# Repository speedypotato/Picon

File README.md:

# Picon
A breakout board for the Raspberry Pi Pico for Yuancon or DIY Controllers

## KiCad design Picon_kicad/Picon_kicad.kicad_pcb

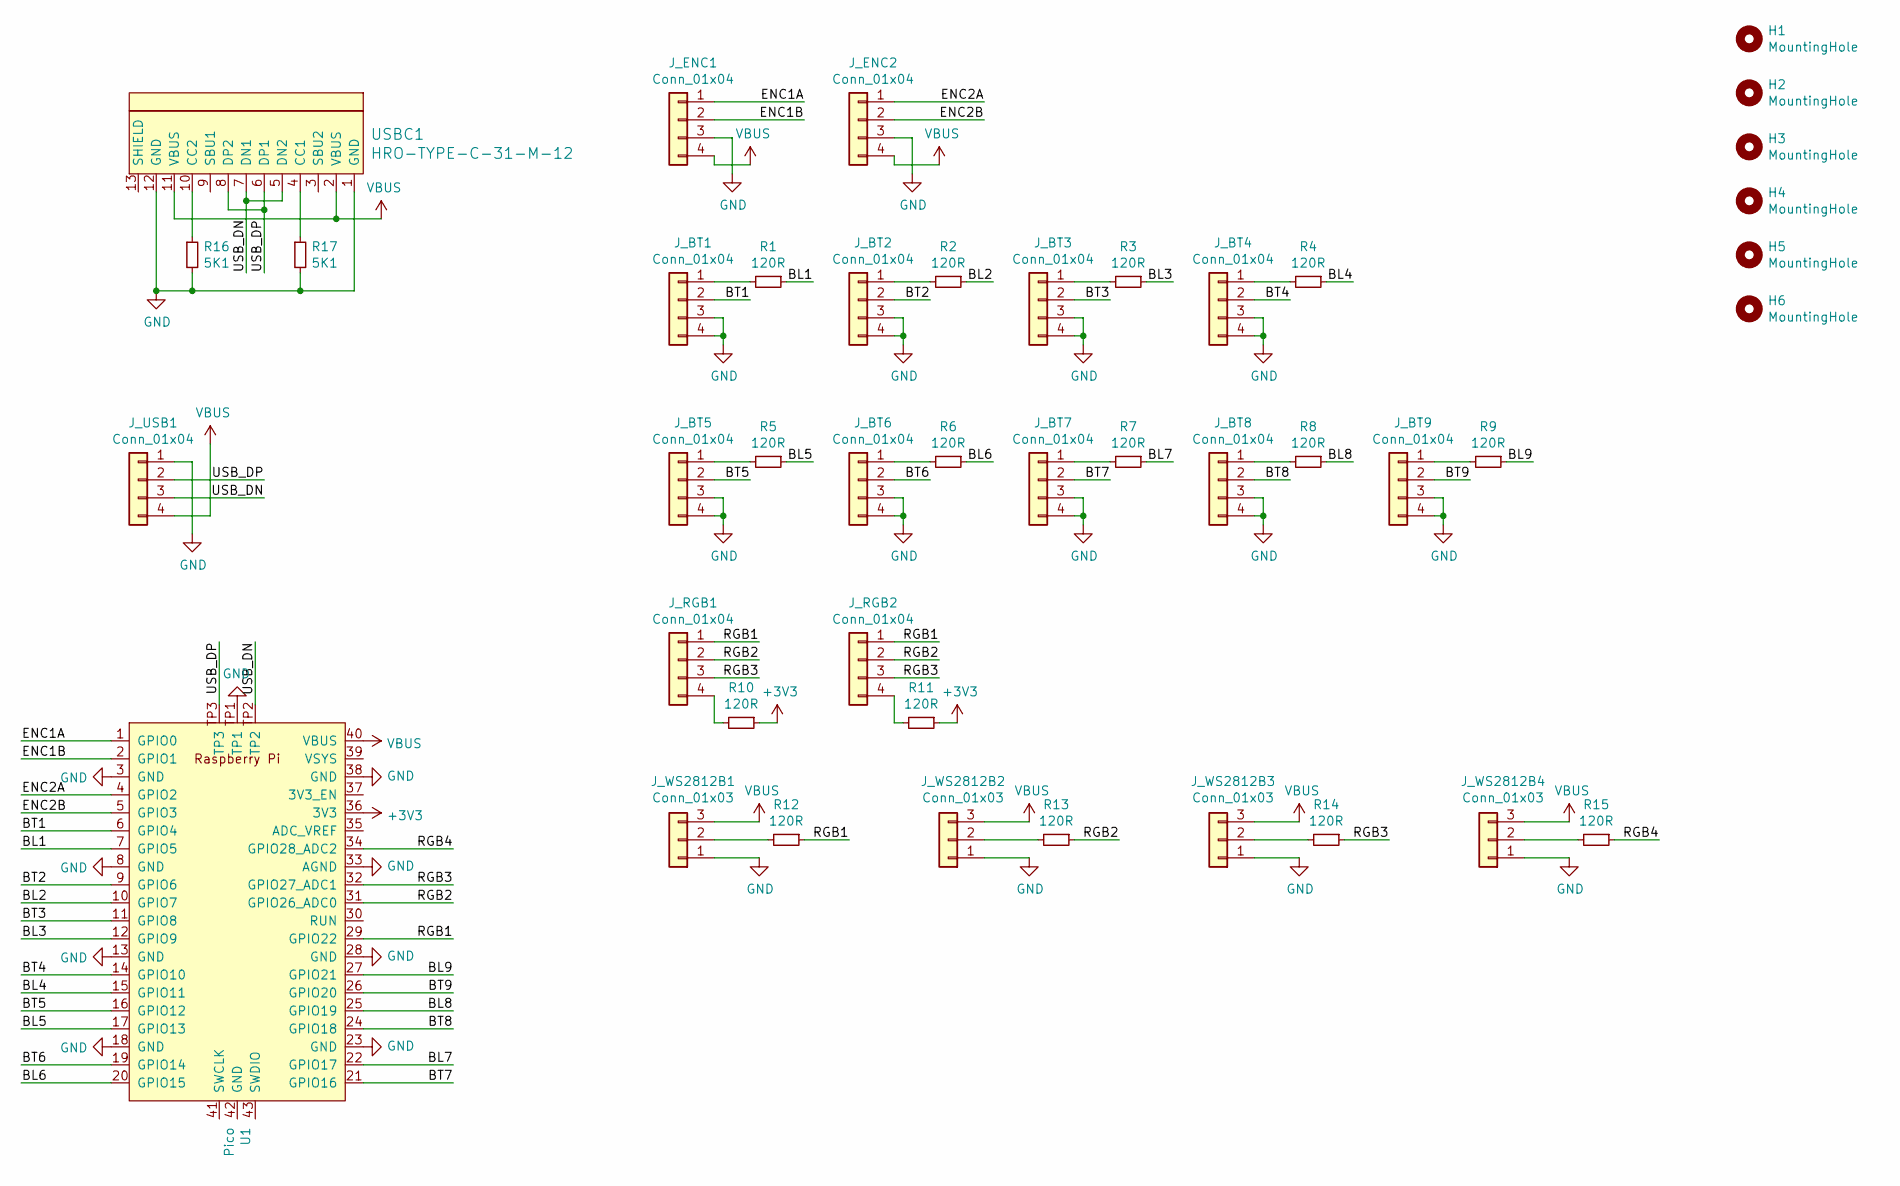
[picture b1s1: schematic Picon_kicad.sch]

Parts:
H1, H2, H3, H4, H5, H6: MountingHole; MountingHole_3mm
J_BT1, J_BT2, J_BT3, J_BT4, J_BT5, J_BT6, J_BT7, J_BT8, J_BT9: Conn_01x04; JST_XH_B4B-XH-A_1x04_P2.50mm_Vertical; LCSC C144395
J_ENC1, J_ENC2: Conn_01x04; JST_XH_B4B-XH-A_1x04_P2.50mm_Vertical; LCSC C144395
J_RGB1, J_RGB2: Conn_01x04; JST_XH_B4B-XH-A_1x04_P2.50mm_Vertical; LCSC C144395
J_USB1: Conn_01x04; JST_XH_B4B-XH-A_1x04_P2.50mm_Vertical; LCSC C144395
J_WS2812B1, J_WS2812B2, J_WS2812B3, J_WS2812B4: Conn_01x03; JST_XH_B3B-XH-A_1x03_P2.50mm_Vertical; LCSC C144394
R1, R2, R3, R4, R5, R6, R7, R8, R9, R10, R11, R12, R13, R14, R15: 120R; R_0603_1608Metric; LCSC C22787
R16, R17: 5K1; R_0603_1608Metric; LCSC C23186
U1: Pico; RPi_Pico_SMD_TH
USBC1: HRO-TYPE-C-31-M-12; HRO-TYPE-C-31-M-12-Assembly; LCSC C165948

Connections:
+3V3: R10.1, R11.1, U1.36 (3V3)
/BL1: R1.1, U1.7 (GPIO5)
/BL2: R2.1, U1.10 (GPIO7)
/BL3: R3.1, U1.12 (GPIO9)
/BL4: R4.1, U1.15 (GPIO11)
/BL5: R5.1, U1.17 (GPIO13)
/BL6: R6.1, U1.20 (GPIO15)
/BL7: R7.1, U1.22 (GPIO17)
/BL8: R8.1, U1.25 (GPIO19)
/BL9: R9.1, U1.27 (GPIO21)
/BT1: J_BT1.2, U1.6 (GPIO4)
/BT2: J_BT2.2, U1.9 (GPIO6)
/BT3: J_BT3.2, U1.11 (GPIO8)
/BT4: J_BT4.2, U1.14 (GPIO10)
/BT5: J_BT5.2, U1.16 (GPIO12)
/BT6: J_BT6.2, U1.19 (GPIO14)
/BT7: J_BT7.2, U1.21 (GPIO16)
/BT8: J_BT8.2, U1.24 (GPIO18)
/BT9: J_BT9.2, U1.26 (GPIO20)
/ENC1A: J_ENC1.1, U1.1 (GPIO0)
/ENC1B: J_ENC1.2, U1.2 (GPIO1)
/ENC2A: J_ENC2.1, U1.4 (GPIO2)
/ENC2B: J_ENC2.2, U1.5 (GPIO3)
/RGB1: J_RGB1.1, J_RGB2.1, R12.1, U1.29 (GPIO22)
/RGB2: J_RGB1.2, J_RGB2.2, R13.1, U1.31 (GPIO26_ADC0)
/RGB3: J_RGB1.3, J_RGB2.3, R14.1, U1.32 (GPIO27_ADC1)
/RGB4: R15.1, U1.34 (GPIO28_ADC2)
/USB_DN: J_USB1.3, U1.TP2, USBC1.5 (DN2), USBC1.7 (DN1)
/USB_DP: J_USB1.2, U1.TP3, USBC1.6 (DP1), USBC1.8 (DP2)
GND: J_BT1.3, J_BT1.4, J_BT2.3, J_BT2.4, J_BT3.3, J_BT3.4, J_BT4.3, J_BT4.4, J_BT5.3, J_BT5.4, J_BT6.3, J_BT6.4, J_BT7.3, J_BT7.4, J_BT8.3, J_BT8.4, J_BT9.3, J_BT9.4, J_ENC1.3, J_ENC2.3, J_USB1.1, J_WS2812B1.1, J_WS2812B2.1, J_WS2812B3.1, J_WS2812B4.1, R16.2, R17.2, U1.3 (GND), U1.8 (GND), U1.13 (GND), U1.18 (GND), U1.23 (GND), U1.28 (GND), U1.33 (AGND), U1.38 (GND), U1.TP1, USBC1.1 (GND), USBC1.12 (GND)
unnamed: J_BT1.1, R1.2
unnamed: J_BT2.1, R2.2
unnamed: J_BT3.1, R3.2
unnamed: J_BT4.1, R4.2
unnamed: J_BT5.1, R5.2
unnamed: J_BT6.1, R6.2
unnamed: J_BT7.1, R7.2
unnamed: J_BT8.1, R8.2
unnamed: J_BT9.1, R9.2
unnamed: J_RGB1.4, R10.2
unnamed: J_RGB2.4, R11.2
unnamed: J_WS2812B1.2, R12.2
unnamed: J_WS2812B2.2, R13.2
unnamed: J_WS2812B3.2, R14.2
unnamed: J_WS2812B4.2, R15.2
unnamed: R16.1, USBC1.10 (CC2)
unnamed: R17.1, USBC1.4 (CC1)
VBUS: J_ENC1.4, J_ENC2.4, J_USB1.4, J_WS2812B1.3, J_WS2812B2.3, J_WS2812B3.3, J_WS2812B4.3, U1.40 (VBUS), USBC1.2 (VBUS), USBC1.11 (VBUS)

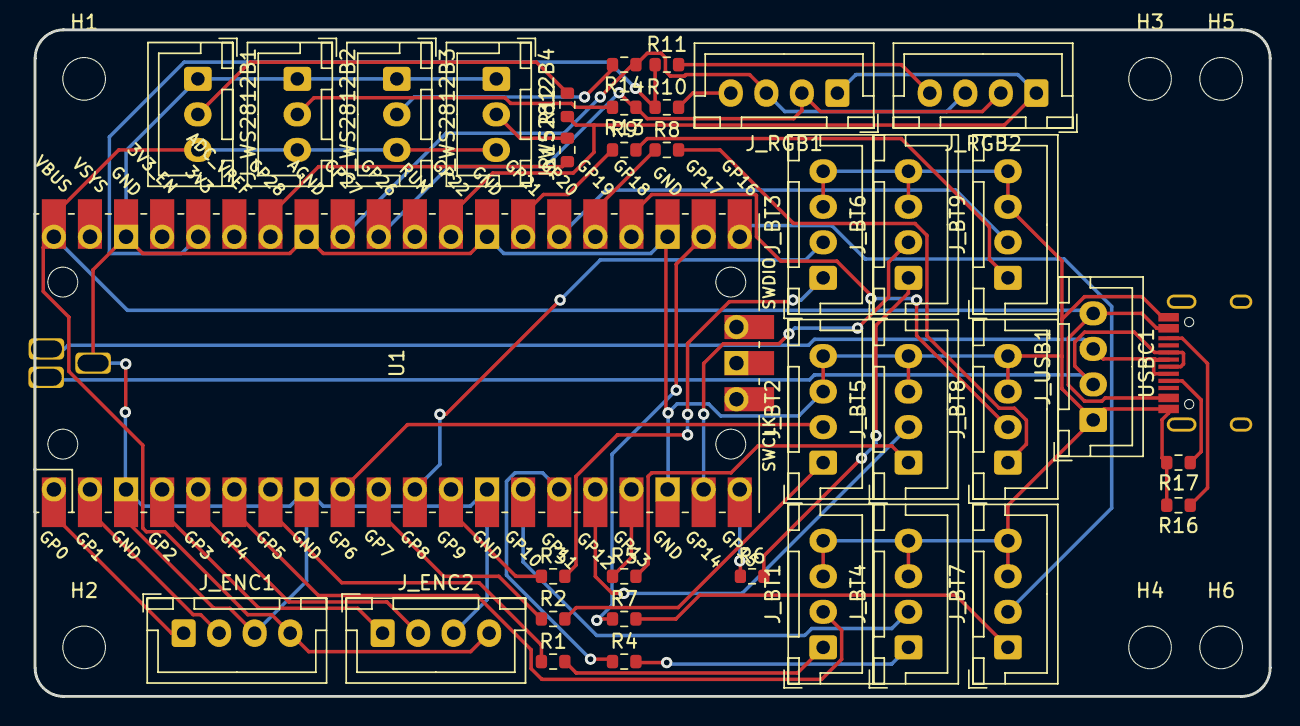
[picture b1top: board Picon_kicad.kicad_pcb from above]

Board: 2 copper layers, 86.9 x 46.9 mm, 43 parts (0 on the bottom side), 48 nets.

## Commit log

2021-09-18 v0.1 | Initial upload, incomplete
2021-09-18 v0.2 | Rudimentary PCB layout
